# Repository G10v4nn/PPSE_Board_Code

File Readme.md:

# Usb data logger
This project was done as a final paper in the electronic systems design and prototyping course. In the **document** folder you can read the report explaining the project and the schematics of the electronic part. In the other two folders are the files for the hardware and firmware design.

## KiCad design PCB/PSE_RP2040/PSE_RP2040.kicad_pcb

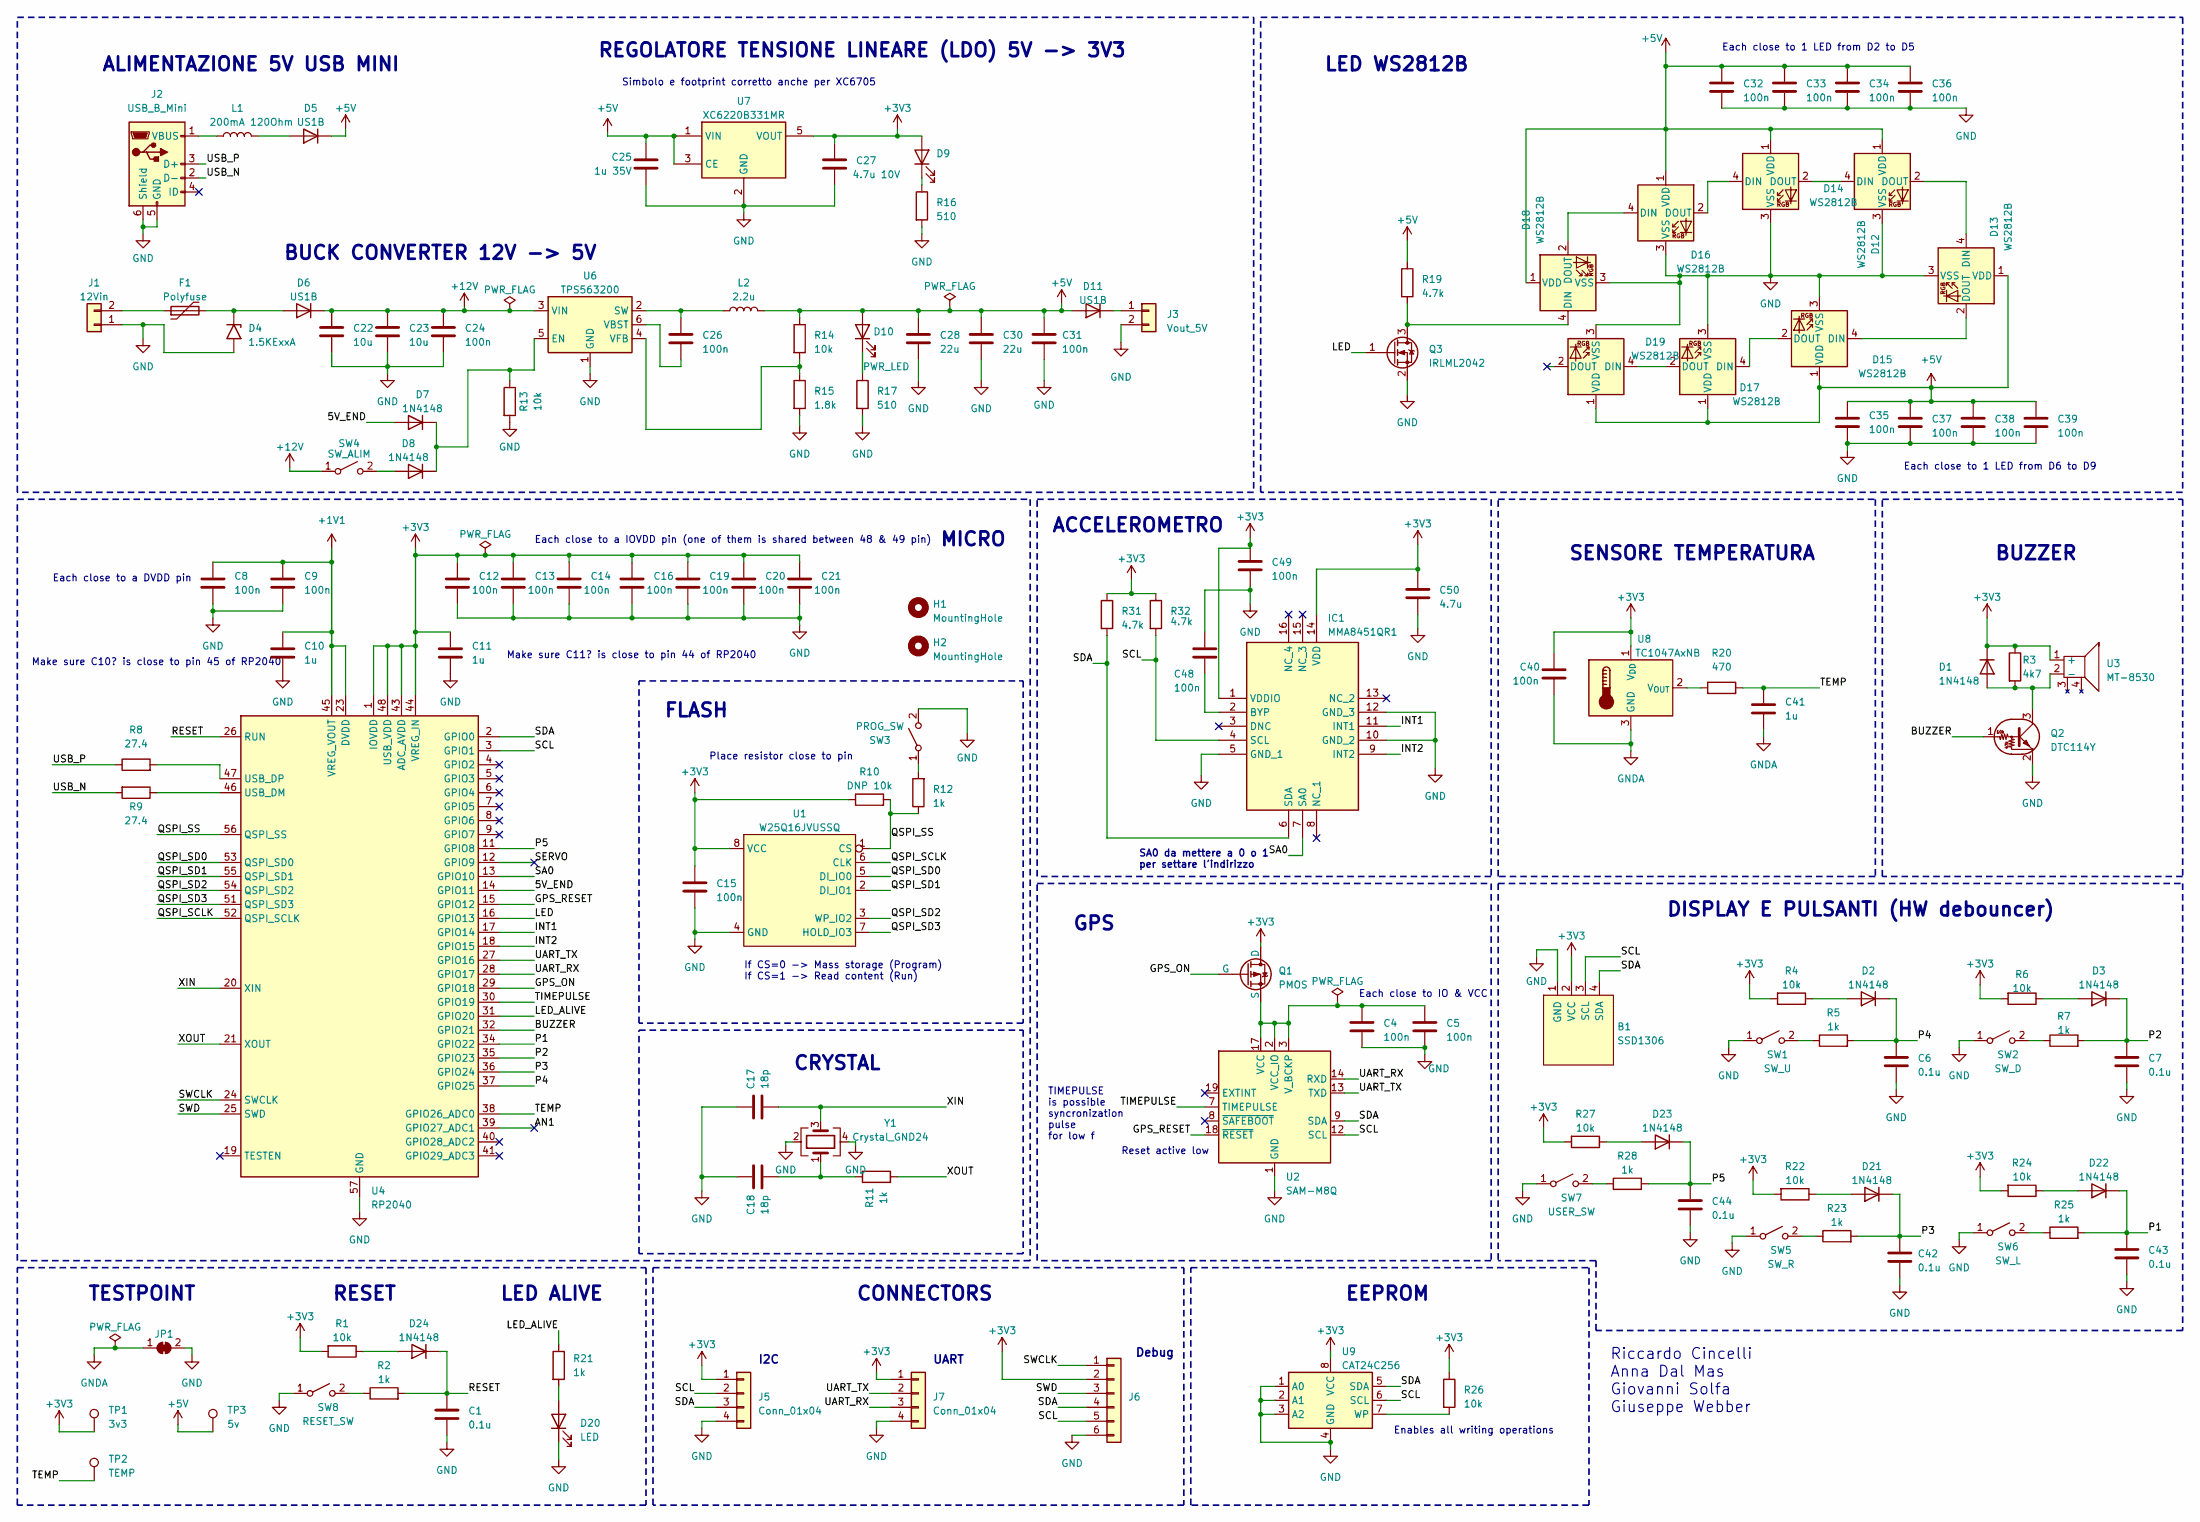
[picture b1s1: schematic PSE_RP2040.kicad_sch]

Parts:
B1: SSD1306; 128x64OLED
C1, C6, C7, C42, C43, C44: 0.1u; C_0603_1608Metric
C4, C5, C8, C9, C12, C13, C14, C15, C16, C19, C20, C21, C24, C26, C31, C32, C33, C34, C35, C36, C37, C38, C39, C40, C48, C49: 100n; C_0603_1608Metric
C10, C11, C41: 1u; C_0603_1608Metric
C17, C18: 18p; C_0603_1608Metric
C22, C23: 10u; CP_Radial_D6.3mm_P2.50mm
C25: 1u 35V; CP_Radial_D6.3mm_P2.50mm
C27: 4.7u 10V; CP_Radial_D6.3mm_P2.50mm
C28, C30: 22u; C_0603_1608Metric
C50: 4.7u; C_0603_1608Metric
D1, D2, D3, D7, D8, D21, D22, D23, D24: 1N4148; Nexperia_CFP3_SOD-123W
D4: 1.5KExxA; D_SMC
D5, D6, D11: US1B; D_SMA
D9, D10: PWR_LED; LED_0603_1608Metric
D12, D13, D14, D15, D16, D17, D18, D19: WS2812B; LED_WS2812B_PLCC4_5.0x5.0mm_P3.2mm
D20: LED; LED_0603_1608Metric
F1: Polyfuse; FUSC5141X200N
H1, H2: MountingHole; MountingHole_3mm
IC1: MMA8451QR1; MMA8452QT; Manufacturer_Part_Number MMA8451QR1; Mouser Part Number 841-MMA8451QR1
J1: 12Vin; 282834-2_1
J2: USB_B_Mini; USB_Mini-B_Wuerth_65100516121_Horizontal
J3: Vout_5V; 282834-2_1
J5, J7: Conn_01x04; PinSocket_1x04_P2.54mm_Vertical
J6: Conn_01x06; PinSocket_1x06_P2.54mm_Vertical
JP1: SolderJumper_2_Bridged; SolderJumper-2_P1.3mm_Bridged_Pad1.0x1.5mm
L1: 200mA 120Ohm; L_0603_1608Metric
L2: 2.2u; LQH44PN100MJ0L
Q1: PMOS; SOT95P237X112-3N
Q2: DTC114Y; SOT-23
Q3: IRLML2042; SOT-23
R1, R4, R6, R13, R14, R22, R24, R26, R27: 10k; R_0603_1608Metric
R2, R5, R7, R11, R12, R21, R23, R25, R28: 1k; R_0603_1608Metric
R3: 4k7; R_0603_1608Metric
R8, R9: 27.4; R_0603_1608Metric
R10: DNP 10k; R_0603_1608Metric
R15: 1.8k; R_0603_1608Metric
R16, R17: 510; R_0603_1608Metric
R19, R31, R32: 4.7k; R_0603_1608Metric
R20: 470; R_0603_1608Metric
SW1: SW_U; SW_PUSH_6mm_H5mm
SW2: SW_D; SW_PUSH_6mm_H5mm
SW3: PROG_SW; SW_PUSH_6mm_H5mm
SW4: SW_ALIM; SW_PUSH_6mm_H5mm
SW5: SW_R; SW_PUSH_6mm_H5mm
SW6: SW_L; SW_PUSH_6mm_H5mm
SW7: USER_SW; SW_PUSH_6mm_H5mm
SW8: RESET_SW; SW_PUSH_6mm_H5mm
TP1: 3v3; TestPoint_Keystone_5005-5009_Compact
TP2: TEMP; TestPoint_Keystone_5005-5009_Compact
TP3: 5v; TestPoint_Keystone_5005-5009_Compact
U1: W25Q16JVUSSQ; SOIC127P600X175-8N
U2: SAM-M8Q; ublox_SAM-M8Q
U3: MT-8530
U4: RP2040; QFN-56-1EP_7x7mm_P0.4mm_EP3.2x3.2mm
U6: TPS563200; SOT-23-6
U7: XC6220B331MR; SOT-23-5
U8: TC1047AxNB; SOT-23
U9: CAT24C256; SOIC127P790X216-8N
Y1: Crystal_GND24; Crystal_SMD_3225-4Pin_3.2x2.5mm_HandSoldering

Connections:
+1V1: C8.1, C9.1, C10.1, U4.23 (DVDD), U4.45 (VREG_VOUT), U4.50 (DVDD)
+3V3: B1.2 (VCC), C11.1, C12.1, C13.1, C14.1, C15.1, C16.1, C19.1, C20.1, C21.1, C27.1, C40.1, C49.1, C50.1, D1.1 (K), D9.2 (A), IC1.1 (VDDIO), IC1.14 (VDD), J5.1, J6.2, J7.1, Q1.1 (D), R1.2, R3.1, R4.2, R6.2, R10.1, R22.2, R24.2, R26.1, R27.2, R31.1, R32.1, TP1.1, U1.8 (VCC), U3.1 (+), U4.1 (IOVDD), U4.10 (IOVDD), U4.22 (IOVDD), U4.33 (IOVDD), U4.42 (IOVDD), U4.43 (ADC_AVDD), U4.44 (VREG_IN), U4.48 (USB_VDD), U4.49 (IOVDD), U7.5 (VOUT), U8.1 (V_{DD}), U9.8 (VCC)
+5V: C25.1, C28.1, C30.1, C31.1, C32.1, C33.1, C34.1, C35.1, C36.1, C37.1, C38.1, C39.1, D5.1 (K), D10.2 (A), D11.2 (A), D12.1 (VDD), D13.1 (VDD), D14.1 (VDD), D15.1 (VDD), D16.1 (VDD), D17.1 (VDD), D18.1 (VDD), D19.1 (VDD), L2.2, R14.1, R19.1, TP3.1, U7.1 (VIN), U7.3 (CE)
+12V: C22.1, C23.1, C24.1, D6.1 (K), SW4.1 (A), U6.3 (VIN)
/5V_END: D7.2 (A), U4.14 (GPIO11)
/AN1: U4.39 (GPIO27_ADC1)
/BUZZER: Q2.1 (B), U4.32 (GPIO21)
/GPS_ON: Q1.2 (G), U4.29 (GPIO18)
/GPS_RESET: U2.18 (~RESET), U4.15 (GPIO12)
/INT1: IC1.11 (INT1), U4.17 (GPIO14)
/INT2: IC1.9 (INT2), U4.18 (GPIO15)
/LED: Q3.1 (G), U4.16 (GPIO13)
/LED_ALIVE: R21.1, U4.31 (GPIO20)
/P1: C43.1, D22.1 (K), R25.2, U4.34 (GPIO22)
/P2: C7.1, D3.1 (K), R7.2, U4.35 (GPIO23)
/P3: C42.1, D21.1 (K), R23.2, U4.36 (GPIO24)
/P4: C6.1, D2.1 (K), R5.2, U4.37 (GPIO25)
/P5: C44.1, D23.1 (K), R28.2, U4.11 (GPIO8)
/QSPI_SCLK: U1.6 (CLK), U4.52 (QSPI_SCLK)
/QSPI_SD0: U1.5 (DI_IO0), U4.53 (QSPI_SD0)
/QSPI_SD1: U1.2 (DI_IO1), U4.55 (QSPI_SD1)
/QSPI_SD2: U1.3 (WP_IO2), U4.54 (QSPI_SD2)
/QSPI_SD3: U1.7 (HOLD_IO3), U4.51 (QSPI_SD3)
/QSPI_SS: R10.2, R12.1, U1.1 (CS), U4.56 (QSPI_SS)
/RESET: C1.1, D24.1 (K), R2.2, U4.26 (RUN)
/SA0: IC1.7 (SA0), U4.13 (GPIO10)
/SCL: B1.3 (SCL), IC1.4 (SCL), J5.2, J6.5, R32.2, U2.12 (SCL), U4.3 (GPIO1), U9.6 (SCL)
/SDA: B1.4 (SDA), IC1.6 (SDA), J5.3, J6.4, R31.2, U2.9 (SDA), U4.2 (GPIO0), U9.5 (SDA)
/SERVO: U4.12 (GPIO9)
/SWCLK: J6.1, U4.24 (SWCLK)
/SWD: J6.3, U4.25 (SWD)
/TEMP: C41.1, R20.2, TP2.1, U4.38 (GPIO26_ADC0)
/TIMEPULSE: U2.7 (TIMEPULSE), U4.30 (GPIO19)
/UART_RX: J7.3, U2.14 (RXD), U4.28 (GPIO17)
/UART_TX: J7.2, U2.13 (TXD), U4.27 (GPIO16)
/USB_N: J2.2 (D-), R9.2
/USB_P: J2.3 (D+), R8.1
/XIN: C17.2, U4.20 (XIN), Y1.3
/XOUT: R11.2, U4.21 (XOUT)
GND: B1.1 (GND), C1.2, C4.2, C5.2, C6.2, C7.2, C8.2, C9.2, C10.2, C11.2, C12.2, C13.2, C14.2, C15.2, C16.2, C17.1, C18.1, C19.2, C20.2, C21.2, C22.2, C23.2, C24.2, C25.2, C27.2, C28.2, C30.2, C31.2, C32.2, C33.2, C34.2, C35.2, C36.2, C37.2, C38.2, C39.2, C42.2, C43.2, C44.2, C48.1, C49.2, C50.2, D4.2 (A2), D12.3 (VSS), D13.3 (VSS), D14.3 (VSS), D15.3 (VSS), D16.3 (VSS), D17.3 (VSS), D18.3 (VSS), D19.3 (VSS), D20.1 (K), IC1.5 (GND_1), IC1.10 (GND_2), IC1.12 (GND_3), J1.1, J2.5 (GND), J2.6 (Shield), J3.2, J5.4, J6.6, J7.4, JP1.2 (B), Q2.2 (E), Q3.2 (S), R13.2, R15.2, R16.2, R17.2, SW1.1 (A), SW2.1 (A), SW3.2 (B), SW5.1 (A), SW6.1 (A), SW7.1 (A), SW8.1 (A), U1.4 (GND), U2.1 (GND), U2.4 (GND), U2.5 (GND), U2.6 (GND), U2.10 (GND), U2.11 (GND), U2.15 (GND), U2.16 (GND), U2.20 (GND), U4.57 (GND), U6.1 (GND), U7.2 (GND), U9.1 (A0), U9.2 (A1), U9.3 (A2), U9.4 (GND), Y1.2, Y1.4
GNDA: C40.2, C41.2, JP1.1 (A), U8.3 (GND)
unnamed: C18.2, R11.1, Y1.1
unnamed: D1.2 (A), Q2.3 (C), R3.2, U3.2 (-)
unnamed: D2.2 (A), R4.1
unnamed: D3.2 (A), R6.1
unnamed: D4.1 (A1), D6.2 (A), F1.2
unnamed: D5.2 (A), L1.2
unnamed: D7.1 (K), D8.1 (K), R13.1, U6.5 (EN)
unnamed: D8.2 (A), SW4.2 (B)
unnamed: D9.1 (K), R16.1
unnamed: D10.1 (K), R17.1
unnamed: D11.1 (K), J3.1
unnamed: D12.4 (DIN), D14.2 (DOUT)
unnamed: D12.2 (DOUT), D13.4 (DIN)
unnamed: D13.2 (DOUT), D15.4 (DIN)
unnamed: D14.4 (DIN), D16.2 (DOUT)
unnamed: D15.2 (DOUT), D17.4 (DIN)
unnamed: D16.4 (DIN), D18.2 (DOUT)
unnamed: D17.2 (DOUT), D19.4 (DIN)
unnamed: D18.4 (DIN), Q3.3 (D), R19.2
unnamed: D20.2 (A), R21.2
unnamed: D21.2 (A), R22.1
unnamed: D22.2 (A), R24.1
unnamed: D23.2 (A), R27.1
unnamed: D24.2 (A), R1.1
unnamed: C48.2, IC1.2 (BYP)
unnamed: F1.1, J1.2
unnamed: J2.1 (VBUS), L1.1
unnamed: C4.1, C5.1, Q1.3 (S), U2.2 (VCC_IO), U2.3 (V_BCKP), U2.17 (VCC)
unnamed: R5.1, SW1.2 (B)
unnamed: R7.1, SW2.2 (B)
unnamed: R12.2, SW3.1 (A)
unnamed: R23.1, SW5.2 (B)
unnamed: R25.1, SW6.2 (B)
unnamed: R28.1, SW7.2 (B)
unnamed: R2.1, SW8.2 (B)
unnamed: R9.1, U4.46 (USB_DM)
unnamed: R8.2, U4.47 (USB_DP)
unnamed: C26.1, L2.1, U6.2 (SW)
unnamed: C26.2, U6.6 (VBST)
unnamed: R14.2, R15.1, U6.4 (VFB)
unnamed: R20.1, U8.2 (V_{OUT})
unnamed: R26.2, U9.7 (WP)

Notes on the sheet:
Reset active low
DISPLAY E PULSANTI (HW debouncer)
Each close to IO & VCC
ALIMENTAZIONE 5V USB MINI
RESET
LED ALIVE
I2C
Make sure C10? is close to pin 45 of RP2040
FLASH
If CS=0 -> Mass storage (Program) If CS=1 -> Read content (Run)
REGOLATORE TENSIONE LINEARE (LDO) 5V -> 3V3
Each close to a DVDD pin
Each close to 1 LED from D6 to D9
TIMEPULSE is possible syncronization pulse for low f
Place resistor close to pin
Make sure C11? is close to pin 44 of RP2040
BUZZER
Enables all writing operations
Each close to a IOVDD pin (one of them is shared between 48 & 49 pin)
BUCK CONVERTER 12V -> 5V
Debug
MICRO
Each close to 1 LED from D2 to D5
SA0 da mettere a 0 o 1 per settare l'indirizzo
SENSORE TEMPERATURA
Simbolo e footprint corretto anche per XC6705
CONNECTORS
UART
GPS
ACCELEROMETRO
CRYSTAL
EEPROM
Riccardo Cincelli Anna Dal Mas Giovanni Solfa Giuseppe Webber
LED WS2812B
TESTPOINT

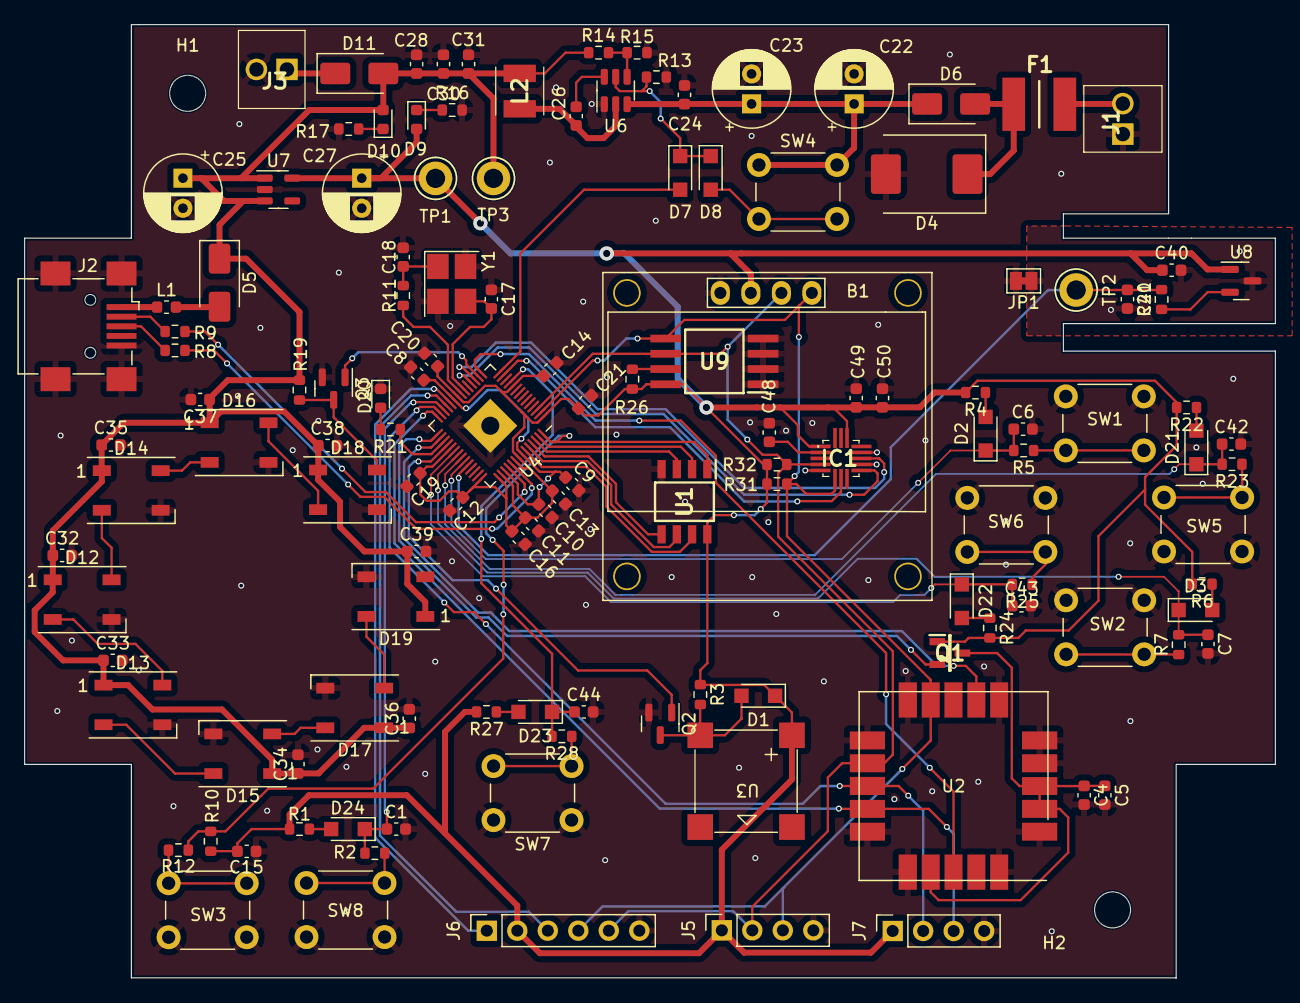
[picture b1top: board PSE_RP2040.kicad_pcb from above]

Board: 2 copper layers, 104.1 x 79.4 mm, 134 parts (0 on the bottom side), 81 nets.

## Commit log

2023-06-05 tiny_usb add
2023-06-06 more example: i2c scan, accelerometer
2023-06-07 added gitignore, resolved problem with CMakeCache
2023-06-07 .gitignore is now working
2023-06-07 gitignore fixing
2023-06-07 reload files
2023-06-07 basic GPS code, no data from GPS
2023-06-08 add the screen test with its lib
2023-06-09 add todo test
2023-06-09 more test, NB: buzzer non funzionate
2023-06-11 added gps code
2023-06-11 add final project
2023-06-11 fixed i2c pin for IMU
2023-06-11 added accelerometer files
2023-06-12 adjust menu
2023-06-12 menu & screen first approach
2023-06-12 included .c and .h sensors. with init and get functions
2023-06-13 minor fixes
2023-06-13 added ringtones for buzzer
2023-06-13 minor
2023-06-13 leds
2023-06-13 fixed .h screen
2023-06-13 added led files, removed useless files
2023-06-13 put FSM structure definition in a .h
2023-06-13 fixed build errors
2023-06-13 added buttons sounds
2023-06-13 problems with buzzer
2023-06-14 fixed buzzer
2023-06-14 screen
2023-06-14 usb files
2023-06-15 added cdc_msc project
2023-06-15 finish
2023-06-15 alleluja, final push (si spera)
2023-07-06 minor changes
2023-07-22 Change folder name
2023-07-22 Update folder
2023-07-24 Added kicad files
2023-07-24 fixing documents
